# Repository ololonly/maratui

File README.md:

<p align="center">
    
    <br><br>
    
</p>

# MaraTUI

An embedded Rust TUI application for the **Lelit Mara X** espresso machine. Runs on an **ESP32** microcontroller driving an **ILI9341 320×240 display** over SPI, reads machine telemetry over UART, and publishes events to MQTT. Includes a host simulator mode for UI development without any hardware.

## Screenshots

| Loading | Dashboard | Debug |
|---------|-----------|-------|
|  |  |  |

## Screens

Navigation cycles between two main screens with a button press. The Debug screen is a hidden overlay.

### Dashboard

The primary screen. Shows all real-time machine data:

- **Mode banner** — COFFEE / STEAM / OFFLINE, color-coded
- **Boiler gauge** — current vs. target temperature with warm→ready color zones and a target marker
- **HX column** — heat-exchanger temperature with a vertical mini-gauge; ideal zone (90–95°C) is always visible
- **HEAT / PUMP indicators** — live status dots
- **Extraction timer** — large countdown in seconds, color shifts white→green→yellow as the shot progresses
- **Shot quality label** — post-extraction assessment (UNDEREXTRACTED / GOOD / PERFECT / LONG SHOT / BLONDING) shown after the pump stops
- **Cup counter** — total shots brewed, received via MQTT

### Graphs

Temperature history chart over a **5-minute rolling window** sampled at 1 Hz:

- Boiler current temperature (yellow)
- Boiler target temperature (red)
- HX temperature (blue)

### Debug (hidden overlay)

Accessible via long press. Shows Wi-Fi and MQTT connection statuses, device info (SSID, RSSI, IP, uptime, free heap), live raw UART frame with activity indicator, and the last 10 telemetry events.

## Getting Started

### Simulator

The simulator runs on your host machine using SDL2 for display emulation — no ESP32 needed.

**Prerequisites:** install SDL2 development libraries for your OS ([installation guide](https://docs.rs/crate/sdl2/latest/source/README.md)).

```bash
make sim          # auto-detects OS
```

Or use platform-specific cargo aliases:

| OS      | Command        |
|---------|----------------|
| Linux   | `cargo sim`    |
| macOS   | `cargo simmac` |
| Windows | `cargo simwin` |

**Keyboard controls:**

| Key          | Action                        |
|--------------|-------------------------------|
| Right / Left | Toggle Dashboard ↔ Graphs     |
| D            | Toggle Debug overlay          |
| Up           | Inject pump-on debug frame    |
| Down         | Inject normal debug frame     |
| Space        | Inject no-water debug frame   |
| M            | Publish manual MQTT event     |

### Device (ESP32)

**Prerequisites:** Rust with the `esp` toolchain channel (pinned in `rust-toolchain.toml`).

```bash
cargo run --release
```

Uses `espflash flash --monitor` as the runner. On startup the firmware:

1. Connects to Wi-Fi using embedded credentials
2. Starts the MQTT client and subscribes to `<prefix>/cup_counter`
3. Streams telemetry to `<prefix>/telemetry` (~1 Hz)
4. Publishes events (shot start/end, water refill, mode change) to `<prefix>/events`
5. Publishes device status (IP, RSSI, uptime, heap) to `<prefix>/status`

## Configuration

Copy `.env.example` to `.env` (git-ignored) and fill in your values:

```bash
cp .env.example .env
```

| Variable | Description |
|---|---|
| `MARATUI_WIFI_SSID` / `_PASSWORD` | Wi-Fi credentials (device build only) |
| `MARATUI_MQTT_ENABLED` | Set `true` to enable MQTT publishing |
| `MARATUI_MQTT_URL` | Broker URL, e.g. `mqtt://192.168.1.x:1883` |
| `MARATUI_MQTT_CLIENT_ID` | Unique client identifier |
| `MARATUI_MQTT_TOPIC_PREFIX` | Topic namespace prefix (default: `mara`) |

> [!NOTE]
> On the ESP32 build (`device` feature), `.env` is parsed by `build.rs` and values are embedded at compile time. On the simulator (`simulator` feature), env values are read at runtime and Wi-Fi is skipped — host networking is used directly for MQTT.

> [!WARNING]
> Wi-Fi and MQTT credentials are stored as plaintext `&'static str` in the flash image. Rotate credentials if the device is shared or its firmware is distributed. See the [Security Considerations](#security-considerations) section below.

## Home Assistant Integration

Build with `--features home-assistant` to enable MQTT Discovery publishing directly from the firmware — no Node-RED or other bridge required. On every MQTT connect, retained discovery configs are published and entities appear in Home Assistant automatically.

```bash
cargo run --release --features home-assistant   # flash
make sim-ha                                      # simulator
```

See [docs/home-assistant.md](docs/home-assistant.md) for the full entity list, MQTT topic reference, and cup counter setup.

## Hardware

Target board: **ESP32 Type-C** with an external **ILI9341** 240×320 TFT display connected over SPI. There is a single physical button.

| Press             | Action                          |
|-------------------|---------------------------------|
| Short             | Toggle Dashboard ↔ Graphs       |
| Short (on loading)| Toggle display backlight        |
| Long              | Enter / exit Debug overlay      |

See [`hardware/`](hardware/) for the KiCad project, PCB renders, Gerber files, and full ESP32 pinout and display wiring.

## Security Considerations

- **Credentials in flash** — Wi-Fi and MQTT credentials are embedded at compile time and extractable from the flash image with standard tools (`strings`, `binwalk`). Rotate if the device is shared.
- **Default broker is public** — `mqtt://broker.emqx.io:1883` is a free public broker with no access control. Set a private broker with authentication before deploying.
- **No TLS** — traffic is plaintext TCP. Switch to `mqtts://` and configure a CA certificate for production use.
- **Open Wi-Fi fallback** — if `MARATUI_WIFI_PASSWORD` is empty, `AuthMethod::None` is used (no encryption). A startup `warn!` names the SSID to make this explicit.

## Roadmap

- Offline mode using NVS storage

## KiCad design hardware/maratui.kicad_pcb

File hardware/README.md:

# MaraTUI PCB

Custom ESP32 controller board for the [Lelit Mara X](https://lelitcoffee.com/product/mara-x/) espresso machine.

## PCB Renders

| Front | Back |
|:-----:|:----:|
|  |  |

## Components

| Ref | Part | Link |
|-----|------|------|
| U1 | ILI9341 2.8" SPI TFT with touch | [Amazon TR](https://www.amazon.com.tr/2-8in%C3%A7-SPI-Dokunmatik-Ekran-Mod%C3%BCl%C3%BC/dp/B0GWFFJBZN) |
| U2 | ESP32-WROOM-32 | [Amazon TR](https://www.amazon.com.tr/ESP32-Wroom-32-Wifi-Bluetooth-Geli%C5%9Ftirme-Kart%C4%B1/dp/B0BT7SW1LF) |
| SW1 | Tactile switch | |
| J1 | Barrel jack (power) | |
| J2 | 3-pin connector (GND + UART) | |

## Wiring

### SPI Display (ILI9341)

| Display Pin | ESP32 GPIO | Notes |
|-------------|------------|-------|
| SCK / CLK   | GPIO18     | VSPI CLK |
| SDA / MOSI  | GPIO21     | VSPI MOSI |
| DC / RS     | GPIO23     | Data/Command select |
| CS          | GPIO19     | Chip Select |
| RST / RESET | GPIO22     | Hardware reset |
| LED / BLK   | GPIO14     | Backlight (HIGH = on) |
| VCC         | 3.3V       | |
| GND         | GND        | |

### UART (Lelit Mara X telemetry)

| Function | ESP32 GPIO | Notes |
|----------|------------|-------|
| TX       | GPIO17     | UART1 TX |
| RX       | GPIO16     | UART1 RX |

### Button

| Button   | ESP32 GPIO | Notes |
|----------|------------|-------|
| SW1      | GPIO12     | Internal pull-up enabled |

Button connects GPIO to **GND** via a tactile switch (active LOW, falling-edge detection).

- Short press (< 500 ms): cycle screens (Dashboard ↔ Graphs)
- Long press (≥ 500 ms): toggle Debug screen

## Custom Libraries

Non-standard components are bundled in `lib/` so the project opens without missing library errors on any machine.

| File | Description |
|------|-------------|
| `lib/symbols/esp32_30pin.kicad_sym` | ESP32-WROOM-32 symbol |
| `lib/symbols/tft_320x240.kicad_sym` | ILI9341 320×240 symbol |
| `lib/footprints/maratui.pretty/ESP32_30pin.kicad_mod` | ESP32 footprint |
| `lib/footprints/maratui.pretty/TFT-320x240.kicad_mod` | TFT display footprint |

## Manufacturing

Gerber files for fabrication: `gerbers/maratui-v1.zip`

Tested with JLCPCB default 2-layer settings.

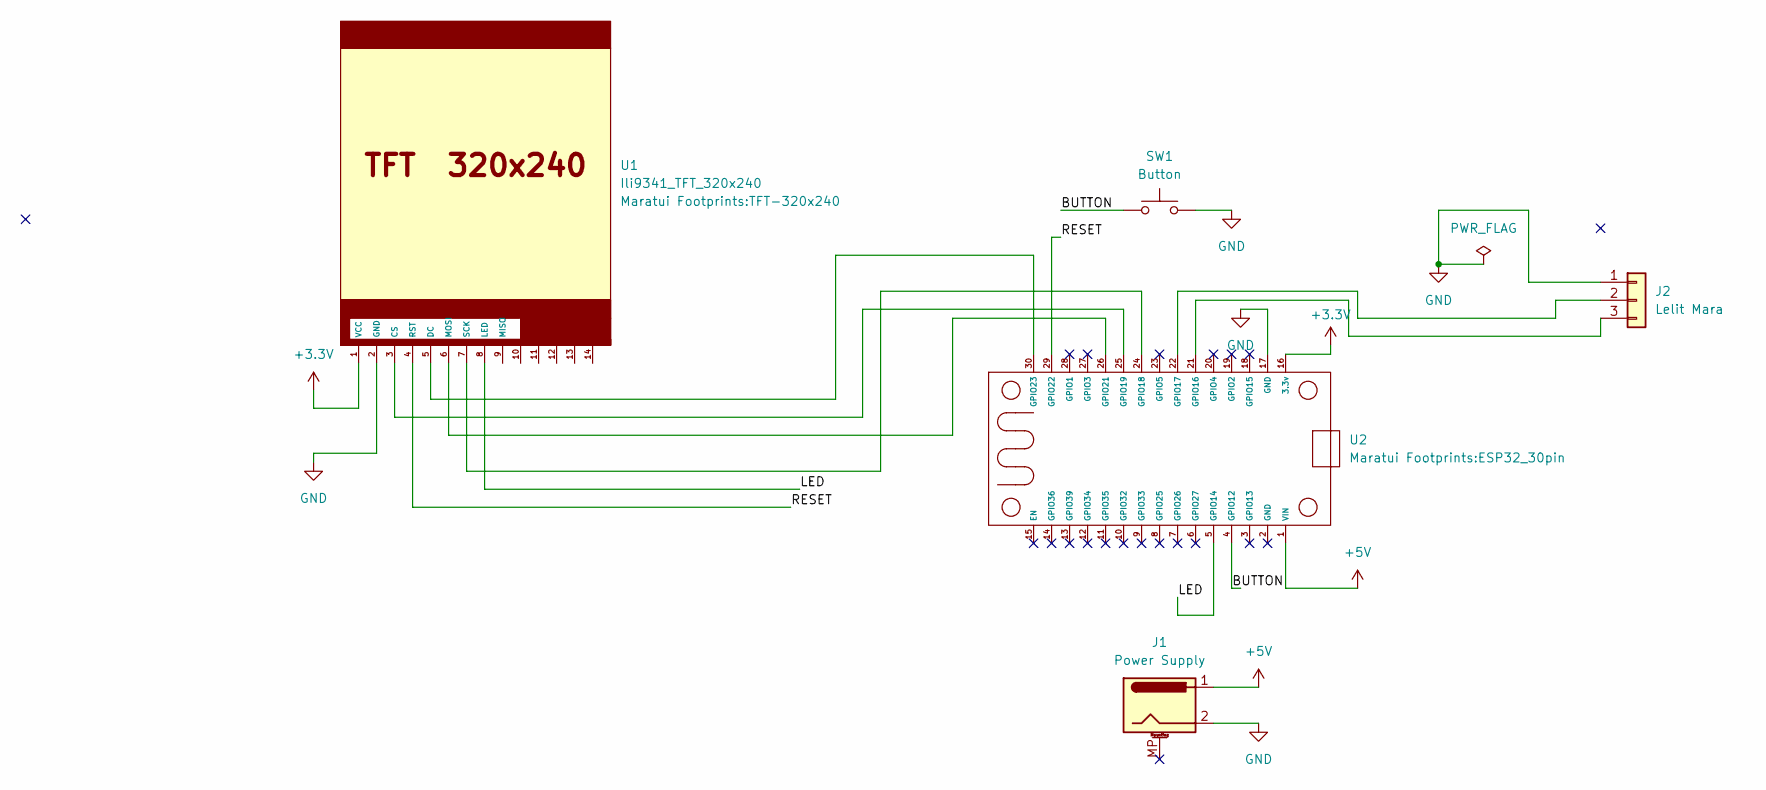
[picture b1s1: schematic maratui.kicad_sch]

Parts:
J1: Power Supply; BarrelJack_CUI_PJ-102AH_Horizontal
J2: Lelit Mara; PinHeader_1x03_P2.54mm_Vertical
SW1: Button; SW_PUSH_6mm
U1: Ili9341_TFT_320x240; TFT-320x240
U2: ESP32_30pin

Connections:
+3.3V: U1.1 (VCC), U2.16 (3.3v)
+5V: J1.1, U2.1 (VIN)
/BUTTON: SW1.1, U2.4 (GPIO12)
/LED: U1.8 (LED), U2.5 (GPIO14)
/RESET: U1.4 (RST), U2.29 (GPIO22)
GND: J1.2, J2.1, SW1.2, U1.2 (GND), U2.17 (GND)
unnamed: J2.2, U2.22 (GPIO17)
unnamed: J2.3, U2.21 (GPIO16)
unnamed: U1.3 (CS), U2.25 (GPIO19)
unnamed: U1.5 (DC), U2.30 (GPIO23)
unnamed: U1.6 (MOSI), U2.26 (GPIO21)
unnamed: U1.7 (SCK), U2.24 (GPIO18)

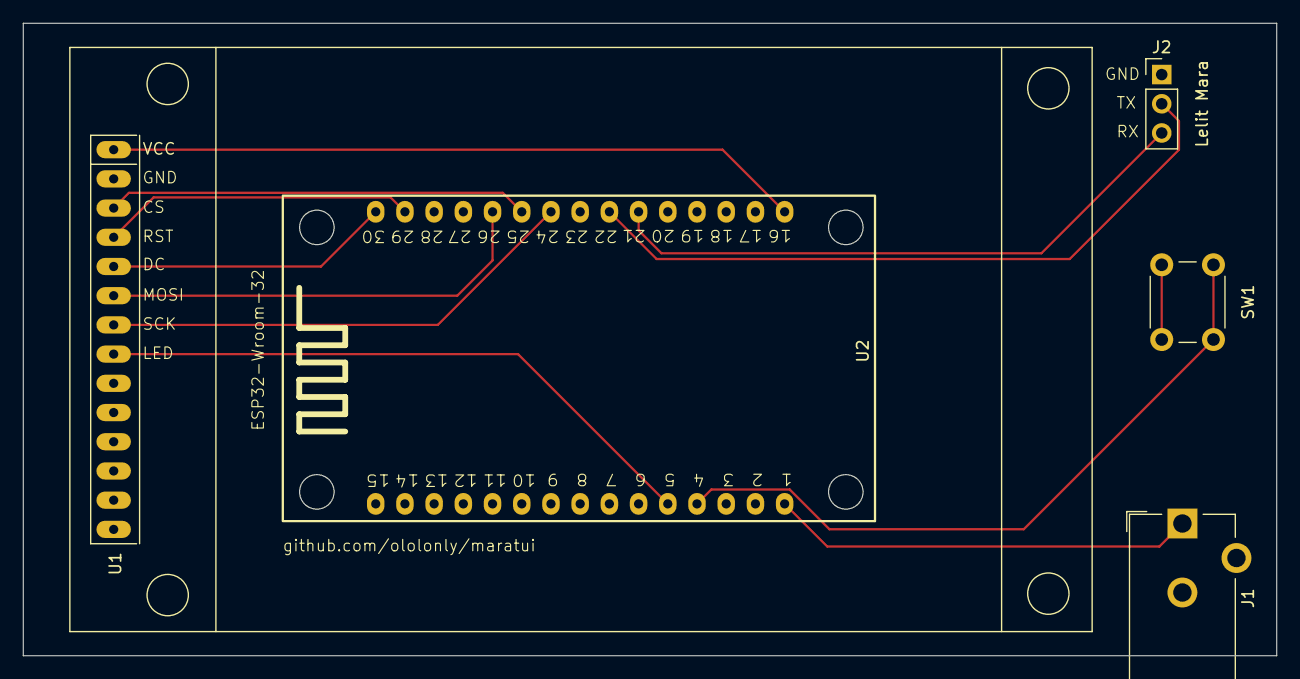
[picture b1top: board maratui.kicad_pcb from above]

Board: 2 copper layers, 109.0 x 55.0 mm, 5 parts (0 on the bottom side), 12 nets.

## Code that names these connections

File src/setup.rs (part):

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use crate::uart_reader::UartReader;
use display_interface_spi::SPIInterface;
use esp_idf_svc::eventloop::EspSystemEventLoop;
use esp_idf_svc::hal::gpio::{AnyIOPin, Gpio22, Gpio23, InterruptType, Output, PinDriver, Pull};
use esp_idf_svc::hal::peripherals::Peripherals;
use esp_idf_svc::hal::spi::{SPI2, SpiConfig, SpiDeviceDriver, SpiDriver};
use esp_idf_svc::hal::units::Hertz;
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
fn get_ili9341<'a>(
    spi_p: SPI2<'a>,
    dc: Gpio23<'a>,
    mosi: esp_idf_svc::hal::gpio::Gpio21<'a>,
    sclk: esp_idf_svc::hal::gpio::Gpio18<'a>,
    cs: Option<esp_idf_svc::hal::gpio::Gpio19<'a>>,
    rst: Gpio22<'a>,
) -> DisplayResult<'a> {
    let sdi = Option::<AnyIOPin>::None; // MISO not used for display

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    let peripherals = Peripherals::take().unwrap();
    let modem = peripherals.modem;
    let spi_p = peripherals.spi2;
    let dc = peripherals.pins.gpio23;
    let mosi = peripherals.pins.gpio21;
    let sclk = peripherals.pins.gpio18;
    let cs = Some(peripherals.pins.gpio19);
    let rst = peripherals.pins.gpio22;
    let uart1 = peripherals.uart1;
    let uart_tx = peripherals.pins.gpio17;
    let uart_rx = peripherals.pins.gpio16;
    let button1_pin = peripherals.pins.gpio12;

    let mut display =
        get_ili9341(spi_p, dc, mosi, sclk, cs, rst).expect("Failed to initialize display");

    let mut backlight = PinDriver::output(peripherals.pins.gpio14).unwrap();
    backlight.set_high().unwrap();

    let mut button1 = PinDriver::input(button1_pin, Pull::Up).unwrap();
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    let stage_start = Instant::now();
    let (tx, rx) = std::sync::mpsc::channel::<TelemetryFrame>();

    info!("Initializing UART1: TX=GPIO17, RX=GPIO16, baud=9600");
    let uart_reader = match UartReader::new(uart1, uart_tx, uart_rx) {
        Ok(reader) => {
            info!("UART1 initialized successfully");
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
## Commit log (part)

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2026-01-12 init commit
2026-01-12 refactor: replace println! with logging functions for better output handling
2026-01-16 chore: remove outdated BUILD_INSTRUCTIONS.md and streamline README for clarity on build modes
2026-01-16 config.toml to lowercase fix
2026-01-16 feat: add embedded graphics support for ESP32 by including necessary draw target and color modules
2026-01-16 deps fix
2026-01-22 qoi Image and telemetry data model
2026-01-22 refactor(ui): update rendering logic to use col3_areas for UI elements
2026-01-22 delete: remove unused rat_chef image assets
    - Deleted rat_chef.png and rat_chef.qoi as they are no longer needed in the project.
2026-01-23 feat(telemetry): integrate UART reader and update telemetry handling
    - Added `uart_reader` module for UART communication.
    - Updated `MaraUi` to display telemetry data from UART, handling cases with and without data.
    - Enhanced `TelemetryFrame` to include raw UART string for better debugging and data representation.
    - Refactored `run_app` to spawn UART task and receive telemetry updates.
2026-01-23 update README: refine upcoming features and enhance clarity
    - Added a section for upcoming UI adjustments, including lifetime graphs and design improvements.
    - Clarified the description of interactive button controls for navigation.
2026-01-26 refactor(ui): introduce screens module and update rendering logic
    - Added a new `screens` module to manage different application screens.
    - Updated the rendering logic in `MaraUi` to utilize the new `Rat` and `Board` structures for screen management.
    - Removed the previous `Screen` enum implementation and its associated methods to streamline the code.
2026-01-28 chore: ili9341 support added. refactored crates usage for ratatui 0.30.0
2026-01-28 feat: implement Dashboard screen and update rendering logic
    - Introduced a new `Dashboard` struct to manage telemetry display.
    - Updated `MaraUi` to render the `Dashboard` when the screen state is set to Dashboard.
    - Refactored rendering logic to streamline the display of telemetry data.
    - Added a debug frame method to `TelemetryFrame` for testing purposes.
2026-01-30 feat(build): enhance build script for ESP32 and add feature flags
    - Updated `build.rs` to check for simulator and device features, providing clearer error messages for simulator usage.
    - Modified `Cargo.toml` to include feature flags for device and simulator builds, improving build flexibility.
    - Updated dependencies in `Cargo.lock` to include new packages and versions, ensuring compatibility with the latest features.
2026-02-02 fix(simulator): use debug telemetry frame on startup
2026-02-03 feat(ui): enhance dashboard status indicators
2026-02-07 chore(config): increase watchdog timeout settings
2026-02-10 build(deps): bump mousefood to 0.4.0
    update the mousefood crate version and align rat screen code with
    current usage by removing unused text imports and icon area binding
2026-02-11 feat: add Makefile with auto-detecting sim target
    `make sim` detects the current OS and runs the appropriate cargo
    simulator alias (sim/simmac/simwin).
    https://claude.ai/code/session_01QvBRuDry56TdicDfa2V1b1
2026-02-11 fix: move ifeq directives to top level in Makefile
    ifeq/else/endif are Make directives, not shell commands — they must
    not be indented as recipe lines. Use a variable instead.
    https://claude.ai/code/session_01QvBRuDry56TdicDfa2V1b1
2026-02-11 refactor(ui): inline screen rendering in draw
    Remove the tab layout and render the active screen directly over the
    full frame area.
    Drop the now-unused tab content helper and related ratatui imports.
2026-02-12 feat(mqtt): add env config and telemetry publishing
    add a shared app config loader for `MARATUI_*` settings with sensible
    defaults and simulator-specific behavior.
    embed `.env` values at build time for device builds and read env values at
    runtime for simulator runs, enabling one configuration model across targets.
    initialize wi-fi and mqtt on esp32 startup and publish telemetry frames to
    `<topic_prefix>/telemetry`; also enable simulator mqtt publishing for debug
2026-02-16 fix(mqtt): wait for broker connect before subscribe
    Delay topic subscription until a Connected event is received to avoid
    subscribing before the client session is ready.
    Also configure the STA netif with a DHCP hostname (`maratui`) by
    wrapping Wi-Fi with explicit netif configuration.
2026-02-17 fix(ui): clear display via terminal backend
    Ensure cleanup uses the same display instance managed by the
    terminal before entering the main loop
2026-03-03 fix(ui): shorten graph legend labels
2026-04-27 feat(ui): add auto-return to previous screen after extraction with backlight timeout
    Implement automatic screen navigation and backlight management based on user activity:
    - Auto-switch to Dashboard when extraction starts, saving the previous screen
    - Auto-return to saved screen 5 seconds after extraction ends
    - Manual navigation during cooldown cancels the scheduled return
    - Backlight turns off after 10 seconds of inactivity (no telemetry or button presses)
    - Track activity timestamps for both telemetry updates and button presses
2026-04-27 feat(ui): add percentage unit label to shot gauge
2026-04-27 feat(ui): add connecting screen and block navigation before telemetry
    Add a new Connecting screen that displays until the first UART telemetry
    frame arrives. Block all navigation (except to Debug screen) until
    telemetry is received to prevent rendering errors from missing data.
    Changes include:
    - New Connecting screen module and render logic
    - Navigation blocking in button handler until first frame
2026-05-04 feat(mqtt): add real-time MQTT connection status monitoring
    Implement bidirectional status channel to track MQTT connection state changes dynamically. Both hardware and simulator setups now receive ConnAck/Disconnected events and update UI accordingly. Preven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
2026-05-04 style: apply rustfmt to setup.rs
    Expand long tuple return in init_networking onto multiple lines.
    https://claude.ai/code/session_0137jQTLwSGjoPGxtHwHrC46
2026-05-06 perf(telemetry): optimize graph rendering and UART reading overhead
    Refactor telemetry graph data handling to eliminate per-render allocations
    by pre-computing graph point vectors once per telemetry frame. Previously,
    the Graphs screen rebuilt three Vec<(f64, f64)> datasets on every render
    from the VecDeque buffers (~900 elements total), causing unnecessary heap
    churn at 60 Hz.
    Changes:
2026-05-06 fix(simulator): replace panic with clean exit on window close
    Previously, closing the SDL simulator window would trigger a panic. This
    change replaces the panic with a proper exit call, allowing the simulator
    to terminate gracefully when the window is closed.
2026-05-06 feat(config): add startup warnings for insecure MQTT and Wi-Fi configurations
    Add warn_insecure() method that logs warnings on startup when:
    - Default public MQTT broker (broker.emqx.io) is detected, exposing telemetry
    - MQTT credentials are sent over plaintext connections (mqtt://, tcp://, ws://)
    - Wi-Fi password is empty, connecting to open networks without encryption
    These warnings make security-sensitive configuration choices explicit in logs
    without blocking functionality for intentional open-network deployments.
2026-05-09 feat(ux): allow backlight toggle via short press during loading
    During the loading phase (before the first UART telemetry frame
    arrives), short button presses had no effect. This change repurposes
    the short press to manually toggle the backlight on/off while the
    device is still initializing.
    - Add `backlight_on: bool` field to `GlobalAppState` (defaults to true)
    - In `handle_button_press`, short press during loading toggles
2026-05-11 style: remove trailing blank lines in fsm.rs
2026-05-11 perf(graph): throttle graph sampling to 1 Hz with 5-minute window
    Replace push_triple with push_sample and a 1-second interval gate.
    Previously every telemetry frame pushed each value three times to
    smooth braille charts; now a single sample is recorded at most once
    per second, tracked via last_graph_sample_at on MachineState.
    The 300-point buffer now represents a true 5-minute rolling window
    instead of ~100 frames of triple-duplicated data.
2026-05-12 docs(readme): rewrite feature overview and expand navigation docs
2026-05-16 fix: Wi-Fi/MQTT reconnection and connection event logging
    Wi-Fi dropped silently and permanently: status showed Connected
    forever while RSSI returned None and MQTT hung in Connecting.
    - Poll Wi-Fi health every 10s via RSSI; emit WifiStatusChanged on
    transitions so the debug screen reflects real state
    - Attempt wifi.connect() (non-blocking ESP-IDF call) every 15s while
    disconnected so the stack re-associates when the AP comes back
2026-05-17 docs(claude): add contributing rules and Node-RED bridge documentation
2026-05-27 chore(claude): add skills directory
2026-06-02 fix(dashboard): update shot quality label for extreme durations
2026-06-02 chore: sponsorship button
2026-06-03 refactor(home-assistant): group state topics under homeassistant/sensor|binary_sensor/maratui/
    Instead of a flat maratui_{id}/state per sensor, state topics are now
    grouped under a shared device subtopic:
    homeassistant/sensor/maratui/{id}
    homeassistant/binary_sensor/maratui/{id}
    Discovery config topics (homeassistant/sensor/maratui_{id}/config) are
    unchanged.
2026-06-06 docs(home-assistant): document direct MQTT Discovery build flag
    Update documentation to explain how to enable native Home Assistant
    integration using the `--features home-assistant` build flag. This
    allows the firmware to publish discovery configurations directly,
    eliminating the need for a Node-RED bridge.
2026-06-08 chore(deps): update Cargo.lock
2026-06-10 chore(skills): migrate ratatui skill to ratatui-tui path
    Remove the old ratatui skill file and update skills-lock.json to
    reference the new ratatui-tui skill sourced from blacktop/dotfiles.
2026-06-20 docs(hardware): expand hardware README with wiring tables and PCB renders
    Add SPI display, UART, and button pinout tables to hardware/README.md,
    include front/back PCB render images, and fix Gerber archive filename
    to maratui-v1.zip.
    Update root README.md to point directly to hardware/ for pinout and
    wiring info, and remove outdated Home Assistant integration and flash
    instructions sections.
2026-06-24 chore(version): bump version to 0.3.5
2026-06-28 fix(debug): remove leading spaces in telemetry display format
